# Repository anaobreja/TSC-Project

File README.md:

# TSC-Project

## BOM (Bill Of Materials)

| Component  | Supplier Link | Datasheet |
|------------|---------------|-----------|
| 112A-TAAR-R03 | [Model](https://store.comet.srl.ro/Catalogue/Product/43497/) | [Datasheet](https://www.snapeda.com/parts/112A-TAAR-R03/Attend/datasheet/) |
| 744043680 | [Model](https://ro.mouser.com/ProductDetail/Wurth-Elektronik/744043680?qs=PGXP4M47uW6VkZq%252BkzjrHA%3D%3D) | [Datasheet](https://www.we-online.com/components/products/datasheet/744043680.pdf) |
| BD5229G-TR | [Model](https://componentsearchengine.com/part-view/BD5229G-TR/ROHM%20Semiconductor) | [Datasheet](https://fscdn.rohm.com/en/products/databook/datasheet/ic/power/voltage_detector/bd52xxg-e.pdf) |
| Capacitor 0402 | [Model](https://ro.mouser.com/c/passive-components/capacitors/ceramic-capacitors/?q=CC0402&srsltid=AfmBOoogjqwwed3xvp6V5-bfVkRuawirfMcnAC47L-UQdC3mnXJk097M) | [Datasheet](https://componentsearchengine.com/Datasheets/2/CC0402MRX5R5BB106.pdf) |
| CPH3225A | [Model](https://www.snapeda.com/parts/CPH3225A/Seiko+Instruments/view-part/?ref=snap) | [Datasheet](https://www.snapeda.com/parts/CPH3225A/Seiko%20Instruments/datasheet/) |
| Custom Button | [Model](https://industry.panasonic.com/global/en/products/control/switch/light-touch/number/evqpuj02k) | [Datasheet](https://industry.panasonic.com/global/en/downloads?tab=catalog&small_g_cd=203&part_no=EVQPUJ02K) |
| DS3231SN | [Model](https://www.snapeda.com/parts/DS3231SN%23/Analog+Devices/view-part/?ref=eda) | [Datasheet](https://www.snapeda.com/parts/DS3231SN%23/Analog%20Devices/datasheet/) |
| ESP32 WROVER 0805 Capacitor | [Model]() | [Datasheet]() |
| ESP32 WROVER BME680 Sensor | [Model](https://www.snapeda.com/parts/BME680/Bosch/view-part/?welcome=home) | [Datasheet](https://www.bosch-sensortec.com/media/boschsensortec/downloads/datasheets/bst-bme680-ds001.pdf) |
| ESP32 WROVER MCP73831 Power Management | [Model](https://www.snapeda.com/parts/BME680/Bosch/view-part/?welcome=home) | [Datasheet](https://www.snapeda.com/parts/MCP73831T-2ACI/OT/Microchip/datasheet/) |
| ESP32C6 Varistor 1812 | [Model]() | [Datasheet]() |
| ESP32C6 WROOM-1-N8| [Model](https://www.snapeda.com/parts/ESP32-C6-WROOM-1-N8/Espressif+Systems/view-part/?ref=eda) | [Datasheet](https://www.snapeda.com/parts/ESP32-C6-WROOM-1-N8/Espressif%20Systems/datasheet/) |
| FH34SRJ-24S-0.5SH | [Model](https://ro.mouser.com/ProductDetail/Hirose-Connector/FH34SRJ-24S-0.5SH99?qs=vcbW%252B4%252BSTIpKBl5ap9J8Fw%3D%3D) | [Datasheet](https://www.snapeda.com/parts/FH34SRJ-24S-0.5SH(99)/Hirose%20Connector/datasheet/) |
| LED Chip 0603 | [Model](https://www.snapeda.com/parts/KP-1608SURCK/Kingbright/view-part/?ref=search&t=LED%200603) | [Datasheet](https://www.snapeda.com/parts/KP-1608SURCK/Kingbright/datasheet/) |
| MAX17048G+T10 | [Model](https://www.snapeda.com/parts/MAX17048G+T10/Analog+Devices/view-part/?ref=eda) | [Datasheet](https://www.snapeda.com/parts/MAX17048G+T10/Analog%20Devices/datasheet/) |
| MBR0530 Schottky Diode | [Model](https://www.snapeda.com/parts/MBR0530/Onsemi/view-part/?ref=snap) | [Datasheet](https://www.snapeda.com/parts/MBR0530/ON%20Semiconductor/datasheet/) |
| PGB1010603MR | [Model](https://www.snapeda.com/parts/PGB1010603MR/Littelfuse/view-part/?ref=eda) | [Datasheet](https://www.snapeda.com/parts/PGB1010603MR/Littelfuse%20Inc./datasheet/) |
| QWIIC Connector | [Model](https://www.snapeda.com/parts/PRT-14417/SparkFun/view-part/) | [Datasheet](https://www.snapeda.com/parts/PRT-14417/SparkFun%20Electronics/datasheet/) |
| RCL CPOL 3528 | [Model](https://www.snapeda.com/parts/CPH3225A/Seiko+Instruments/view-part/?ref=eda) | [Datasheet](https://s3.amazonaws.com/snapeda/datasheet/TAJB475K025RNJ_AVX.pdf) |
| Resistor 0402 | [Model](https://grabcad.com/library/resistor-0402-1) | [Datasheet](https://www.yageo.com/upload/media/product/products/datasheet/rchip/PYu-RC_Group_51_RoHS_L_12.pdf) |
| SI1308EDL-T1-GE3 MOSFET | [Model](https://www.snapeda.com/parts/SI1308EDL-T1-GE3/Vishay+Siliconix/view-part/?welcome=home&ref=eda) | [Datasheet](https://www.snapeda.com/parts/SI1308EDL-T1-GE3/Vishay%20Siliconix/datasheet/) |
| SJ | [Model](https://grabcad.com/library/solder-jumpers-1) | [Datasheet]() |
| USB4110-GF-A | [Model](https://componentsearchengine.com/part-view/USB4110-GF-A/GCT%20(GLOBAL%20CONNECTOR%20TECHNOLOGY)) | [Datasheet](https://gct.co/files/drawings/usb4110.pdf) |
| USBLC6-2SC6Y | [Model](https://www.snapeda.com/parts/USBLC6-2SC6Y/STMicroelectronics/view-part/?welcome=home&ref=eda) | [Datasheet](https://www.snapeda.com/parts/USBLC6-2SC6Y/STMicroelectronics/datasheet/) |
| W25Q512JVEIQ | [Model](https://www.snapeda.com/parts/W25Q512JVEIQ/Winbond+Electronics/view-part/?ref=eda) | [Datasheet](https://www.winbond.com/resource-files/W25Q512JV%20SPI%20RevB%2006252019%20KMS.pdf) |
| XC6220A331MR-G | [Model](https://componentsearchengine.com/part-view/XC6220A331MR-G/Torex) | [Datasheet](https://product.torexsemi.com/system/files/series/xc6220.pdf) |

## Hardware Description  

1. Microcontroller - ESP32-C6-WROOM-1-N8 The ESP32-C6 is the core processing unit responsible for handling all system operations, communication with sensors and modules, and power management.
Architecture: RISC-V 32-bit
Clock Speed: 160 MHz
Wireless Connectivity: 2.4 GHz Wi-Fi 6, Bluetooth 5.0 

2. Power Management & Battery Battery Type: Li-Po (Lithium Polymer)
Capacity: 3.7V, 1800mAh
Charging Circuit: MCP73831T
Input Voltage: 5V via USB-C
Protection Features: Overcharge and deep discharge protection
Voltage Regulator: LDO regulator ensures a stable 3.3V power supply to all components.

3. Display - E-Paper (E-Ink) Screen
Size: 7.5 inches
Resolution: 800x480 pixels
Communication Interface: SPI

4. SD Card Module
Type: MicroSD (Supports FAT32)
Interface: SPI

5. External NOR Flash
Capacity: 64MB
Interface: SPI

6. Environmental Sensor - BME688
Functions: Measures temperature, humidity, air pressure, and gas levels.
Communication Interface: I2C 

7. Real-Time Clock (RTC) - DS3231SN
Functionality: Maintains time and date even when the system is powered off.
Communication Interface: I2C 

8. USB-C Connector & ESD Protection
Functionality: Provides power input and data transfer capability.
Protection: Integrated ESD protection and Schottky diode for reverse polarity safety. 

9. Buttons & User Input
Tactile Push Buttons

10. Communication Interfaces
GPIO: Used for button controls and general I/O operations.
SPI: Used for SD card, external flash memory, and e-paper display.
I2C: Used for the BME688 environmental sensor and DS3231SN RTC module.
UART: Used for debugging and serial communication.
Wi-Fi & Bluetooth: Provided by ESP32-C6, allowing wireless connectivity.

## Power Consumption Estimation

| Component                | Current Draw (mA) | Voltage (V) | Power (mW) |
|--------------------------|------------------|-------------|------------|
| ESP32-C6 (Wi-Fi active)  |200               |3.3          |660
| E-Paper Display (Updating)               | 40               | 3.3         | 132        |
| BME688 Sensor (Measuring)| 3.1              | 3.3         | 10.23      |
| RTC Module (Active)      | 0.15             | 3.3         | 0.495      |
| SD Card (Active)         | 50               | 3.3         | 165        |
| Externar NOR Flash       | 25               | 3.3         | 82.5       |
| Total Estimated Power Consumption               | ~318.5mA         | 3.3         | 1050.72    |

## ESP32-C6 Pin Mapping  

| Component                | ESP32-C6 Pin(s) | Interface | Purpose |
|--------------------------|----------------|-----------|---------|
| **E-Paper Display**      | IO7 (MOSI), IO6 (SCK), IO10 (CS), IO5 (DC), IO23 (RST), IO3 (BUSY) | SPI | Transfers image data to the display and controls its state. |
| **MicroSD Card**         | IO7 (MOSI), IO6 (SCK), IO4 (SS_SD), IO2 (MISO) | SPI | Allows storage and retrieval of e-book files. |
| **Environmental Sensor (BME688)** | IO21 (SDA), IO22 (SCL) | I2C | Reads temperature, humidity, pressure, and air quality data. |
| **RTC Module (DS3231)**  | IO21 (SDA), IO22 (SCL), IO18 (RST), IO1 (32KHz), IO0 (INT_RTC) | I2C | Keeps track of time even when ESP32 is off. |
| **External NOR Flash**   | IO11 (CS), IO6 (SCK), IO2 (MISO), IO7 (MOSI) | SPI | Provides additional storage for application data. |
| **Battery Monitoring**   | IO21 (SDA), IO22 (SCL) | I2C | Reads battery voltage and charge status. |
| **USB-C Connection**     | GPIOs through voltage regulation | USB | Powers and programs the ESP32-C6. |
| **Control Buttons**      | IO9 (BOOT), IO15 (CHANGE), EN (RESET) | GPIO | User input for device interactions. |
|

## Additional Design Notes
### Footprint Adjustments
Diode (SMD-Hole): The original footprint had pad holes that were too small, which would have caused soldering issues.
The pad size was updated to 35mil x 190mil to ensure manufacturability and a reliable electrical connection.

U4 – MAX17048G+T10: The VBAT power trace was designed with a width of 0.3mm, based on implementation constraints
 However, the footprint had pin widths of only 0.27mm, resulting in asymmetry and inconsistent routing. The pin sizes
 were adjusted to match the trace width and maintain design symmetry.

### Routing & Ground Plane
Power traces were routed only on the top layer, which required the use of approximately 150 vias to allow for
signal routing on the bottom layer.

The ground plane (GND) was added after routing was completed, applied to both top and bottom layers to ensure
low-impedance grounding and reduced EMI.

### Component Placement
External ports were carefully aligned with the custom OpenBook enclosure to ensure proper fit and accessibility.

Test pads (TPs) were placed near the edges of the board and close to major components for easy debugging access.

100nF decoupling capacitors were placed close to power pins of ICs, in line with standard design practices for
noise reduction.

### Schematic & 3D Model Issues
A net named GND1 appeared in the schematic but was not visible or functionally connected. This was likely an
artifact introduced during the design process.

After routing was completed, updates to 3D models caused pin order reversals in some 2-pin components, breaking
existing connections. This was corrected by rotating the affected models by 180° and realigning the pins.

### Enclosure & 3D Integration
An alternative version of the OpenBook enclosure was created, including a custom color for personalization.

3D components were imported using two methods, depending on how frequently each part appeared in the schematic.

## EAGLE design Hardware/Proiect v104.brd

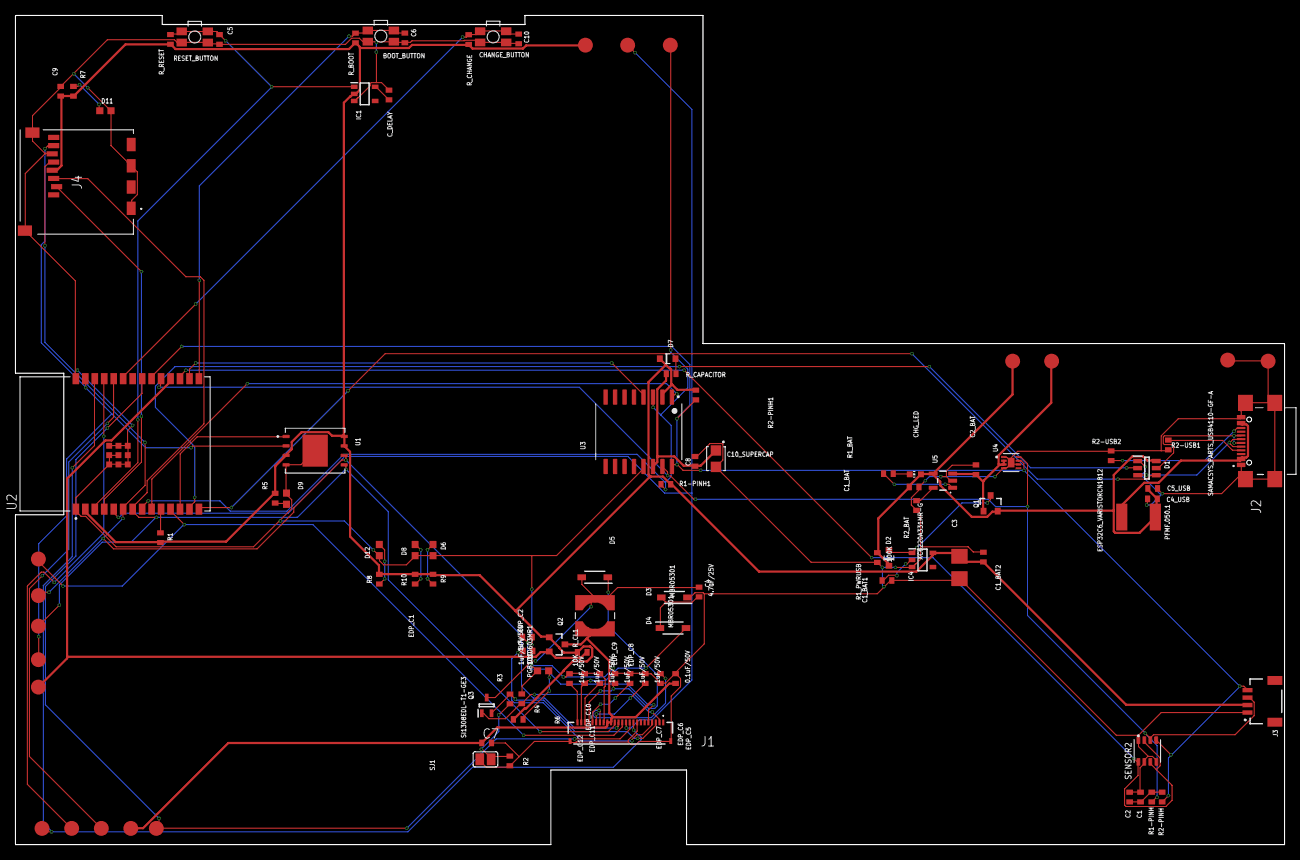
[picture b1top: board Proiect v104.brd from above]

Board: 2 copper layers, 170.2 x 111.2 mm, 103 parts (0 on the bottom side), 63 nets.

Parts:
BOOT_BUTTON: BUTTON_CUSYOMV1; MYBUTTON
C1, C2, C4_USB, C8, C9: 100nF; ESP32_WROVER_EAGLE-LTSPICE_C0402
C1_BAT, C1_BAT1, C1_BAT2, C2_BAT, C5_USB: 4.7uF; ESP32_WROVER_EAGLE-LTSPICE_C0402
C3: 100uF TANT; RCL_CT3528
C4: 4.7uF/25V; ESP32_WROVER_EAGLE-LTSPICE_C0402
C5, C6, C10: 1uF; ESP32_WROVER_EAGLE-LTSPICE_C0402
C7: 10uF; ESP32_WROVER_EAGLE-LTSPICE_C0402
C10_SUPERCAP: CPH3225A; CAPCP3225X100N
CHANGE_BUTTON: BUTTON_CUSYOMV1; MYBUTTON
CHG_LED: 1; ADAFRUIT_CHIP-LED0603
C_DELAY: 100nF; ESP32_WROVER_EAGLE-LTSPICE_C0402
D1: USBLC6-2SC6Y1; SOT95P280X145-6N
D2: ESP32_WROVER_AVX---SD0805S020S1R0_AVX_SD0805S020S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; ESP32_WROVER_AVX---SD0805S020S1R0_AVX_SD0805S020S1R0_0
D3, D4, D5: MBR05301; SOD3716X135N
D6, D8, D9, D10, D11, D12: PGB1010603MR1; DIOC1608X36N
D7: SD805S020S1R0; ESP32_WROVER_AVX---SD0805S020S1R0_AVX_SD0805S020S1R0_0
EDP_C1, EDP_C2, EDP_C6, EDP_C7, EDP_C8, EDP_C9, EDP_C10, EDP_C11, EDP_C12: 1uF/50V; ESP32_WROVER_EAGLE-LTSPICE_C0402
EDP_C5: 0.1uF/50V; ESP32_WROVER_EAGLE-LTSPICE_C0402
IC1: BD5229G-TR; SOT95P280X125-5N
IC4: XC6220A331MR-G; SOT95P280X120-5N
J1: FH34SRJ-24S-0.5SH_99_; FH34SRJ24S05SH99
J2: SAMACSYS_PARTS_USB4110-GF-A; SAMACSYS_PARTS_USB4110GFA
J3: QWIIC_RIGHT_ANGLE; JST04_1MM_RA
J4: 112A-TAAR-R03_ATTEND; 112ATAARR03ATTEND
L1: 68uH; IND_4828-WE-TPC_WRE
PFMF.050.1: ESP32C6_VARISTORCN1812; ESP32C6_VARISTOR_CT/CN1812
Q1, Q2: 20V/4.2A/52mΩ/1.4W; ESP32_WROVER_SPARKFUN-DISCRETESEMI_SOT23-3
Q3: SI1308EDL-T1-GE3; SOT65P210X110-3N
R1, R1-PINH, R1-PINH1, R2-PINH, R2-PINH1, R4, R5, R6, R7, R8, R9, R10: 10K; ESP32_WROVER_EAGLE-LTSPICE_R0402
R1_BAT: 200; ESP32_WROVER_EAGLE-LTSPICE_R0402
R1_PWRUSB: 100K; ESP32_WROVER_EAGLE-LTSPICE_R0402
R2: 2.2; ESP32_WROVER_EAGLE-LTSPICE_R0402
R2-USB1, R2-USB2: 5k1; ESP32_WROVER_EAGLE-LTSPICE_R0402
R2_BAT: 2K; ESP32_WROVER_EAGLE-LTSPICE_R0402
R3: 0.47; ESP32_WROVER_EAGLE-LTSPICE_R0402
RESET_BUTTON: BUTTON_CUSYOMV1; MYBUTTON
R_BOOT: 10K; ESP32_WROVER_EAGLE-LTSPICE_R0402
R_CAPACITOR: 15; ESP32_WROVER_EAGLE-LTSPICE_R0402
R_CHANGE: 10K; ESP32_WROVER_EAGLE-LTSPICE_R0402
R_CL1: 10K; ESP32_WROVER_EAGLE-LTSPICE_R0402
R_RESET: 10K; ESP32_WROVER_EAGLE-LTSPICE_R0402
SENSOR2: BME688; ESP32_WROVER_BME680_PSON80P300X300X100-8N
SJ1: 1; SJ
TP1, TP2, TP3, TP4, TP5, TP6, TP7, TP8, TP9, TP10, TP11, TP12, TP13, TP14, TP15, TP16, TP17: TP; TP20R
U1: W25Q512JVEIQ; SON127P600X800X80-9N
U2: ESP32-C6-WROOM-1-N8; XCVR_ESP32-C6-WROOM-1-N8
U3: DS3231SN#; SOIC127P1032X265-16N
U4: MAX17048G+T10; SON50P200X200X80-9N
U5: MCP73831; ESP32_WROVER_SPARKFUN-IC-POWER_SOT23-5

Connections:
3V3: C1_BAT2.1, C3.+, C9.1, D7.1, IC1.2, IC4.5, J3.2, J4.P4, Q2.1, R1.1, R1-PINH1.2, R2-PINH1.2, R5.2, R6.2, R7.2, R8.2, R9.2, R10.2, R_BOOT.1, R_CHANGE.1, R_CL1.1, R_RESET.1, TP16.3V3, U1.3, U1.7, U1.8, U2.2, U3.2
12C_PW: C1.1, C2.1, R1-PINH.2, R2-PINH.2
32KHZ: U2.9, U3.1
DN: D1.3, J2.A7, J2.B7
DP: D1.5, J2.A6, J2.B6
EPD_3V3: C7.1, EDP_C5.1, J1.15, J1.16, L1.2, Q2.3, TP17.3V3
EPD_3V3_C: Q2.2, R_CL1.2, TP13.3V3, U2.18
EPD_BUSY: J1.9, TP9.3V3, U2.26
EPD_CS: J1.12, TP10.3V3, U2.11
EPD_DC: J1.11, TP11.3V3, U2.5
EPD_RST: J1.10, TP12.3V3, U2.21
FLASH_CS: U1.1, U2.12
GDR: J1.2, Q3.1, R4.1
GND: BOOT_BUTTON.1, BOOT_BUTTON.2, C1.2, C1_BAT.2, C1_BAT1.2, C1_BAT2.2, C2.2, C2_BAT.2, C3.-, C4_USB.2, C5.2, C5_USB.2, C6.2, C7.2, C8.2, C9.2, C10.2, C10_SUPERCAP.2, CHANGE_BUTTON.1, CHANGE_BUTTON.2, C_DELAY.2, D1.1, D3.1, D6.1, D8.1, D9.1, D10.1, D11.1, D12.1, EDP_C1.2, EDP_C2.2, EDP_C5.2, EDP_C6.2, EDP_C7.2, EDP_C8.2, EDP_C9.2, EDP_C10.2, EDP_C11.2, EDP_C12.2, IC1.3, IC4.3, J1.8, J1.17, J1.MP1, J1.MP2, J2.A1, J2.A12, J2.B1, J2.B12, J2.MP1, J2.MP2, J2.MP3, J2.MP4, J3.1, J4.G1, J4.G2, J4.G3, J4.G4, J4.P6, R1_PWRUSB.1, R2.1, R2-USB1.1, R2-USB2.2, R2_BAT.1, R4.2, RESET_BUTTON.1, RESET_BUTTON.2, SENSOR2.1, SENSOR2.5, SENSOR2.7, SJ1.1, TP4.3V3, TP5.3V3, U1.4, U1.9, U2.1, U2.28, U2.29_1, U2.29_2, U2.29_3, U2.29_4, U2.29_5, U2.29_6, U2.29_7, U2.29_8, U2.29_9, U3.13, U4.1, U4.4, U4.6, U4.9, U5.2
GPIO8: R1.2, U2.10
I2C_PW: SENSOR2.2, SENSOR2.6, SENSOR2.8, U2.17
INT_RTC: R1-PINH1.1, TP15.3V3, U2.8, U3.3
IO/BOOT: BOOT_BUTTON.3, BOOT_BUTTON.4, C6.1, R_BOOT.2, U2.15
IO/CHANGE: C10.1, CHANGE_BUTTON.3, CHANGE_BUTTON.4, R_CHANGE.2, U2.23
MISO: J4.P7, TP6.3V3, U1.2, U2.27
MOSI: J1.14, J4.P3, TP7.3V3, U1.5, U2.7
unnamed: J2.A5, R2-USB1.2
unnamed: J2.B5, R2-USB2.1
unnamed: C4.1, D3.2, D4.1
unnamed: EDP_C1.1, J1.4
unnamed: EDP_C2.1, J1.5
unnamed: EDP_C6.1, J1.18
unnamed: EDP_C7.1, J1.19
unnamed: EDP_C8.1, J1.20
unnamed: C1_BAT1.1, IC4.2
unnamed: EDP_C10.1, J1.22
unnamed: D2.2, IC4.1, Q1.3
unnamed: C_DELAY.1, IC1.5
unnamed: R1_BAT.1, U5.1
unnamed: CHG_LED.C, R1_BAT.2
unnamed: D7.2, R_CAPACITOR.2
unnamed: EDP_C12.1, J1.24
unnamed: R2_BAT.2, U5.5
unnamed: D12.2, R8.1
unnamed: D10.2, R6.1
unnamed: D11.2, R7.1
unnamed: D9.2, R5.1
unnamed: D6.2, R9.1
unnamed: D8.2, R10.1
PREVGH: D5.1, EDP_C9.1, J1.21
PREVGL: D4.2, EDP_C11.1, J1.23
RESE: J1.3, Q3.2, R3.2
RESE': R2.2, R3.1, SJ1.2
RESET: C5.1, IC1.1, RESET_BUTTON.3, RESET_BUTTON.4, R_RESET.2, U2.3
RTC_RST: U2.16, U3.4
RX: TP2.3V3, U2.24
SCK: J1.13, J4.P5, TP8.3V3, U1.6, U2.6
SCL: J3.4, R2-PINH.1, R2-PINH1.1, SENSOR2.4, U2.20, U3.16, U4.7
SDA: J3.3, R1-PINH.1, SENSOR2.3, U2.19, U3.15, U4.8
SRC: C4.2, D5.2, L1.1, Q3.3
SS_SD: J4.P2, U2.4
TX: TP1.3V3, U2.25
USB_D+: D1.4, U2.14
USB_D-: D1.2, U2.13
VBAT: C2_BAT.1, Q1.1, TP3.3V3, U4.2, U4.3, U5.3
VBUS: C1_BAT.1, C4_USB.1, C5_USB.1, CHG_LED.A, D1.6, D2.1, PFMF.050.1.2, Q1.2, R1_PWRUSB.2, TP14.3V3, U5.4
VRTC: C8.1, C10_SUPERCAP.1, R_CAPACITOR.1, U3.14
VUSB: J2.A4, J2.A9, J2.B4, J2.B9, PFMF.050.1.1

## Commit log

2025-04-05 Update README.md
    .
2025-04-05 Create LICENSE

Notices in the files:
parts and their libraries:
COPYRIGHT: Copyright (C) 2024 Ultra Librarian. All rights reserved.
